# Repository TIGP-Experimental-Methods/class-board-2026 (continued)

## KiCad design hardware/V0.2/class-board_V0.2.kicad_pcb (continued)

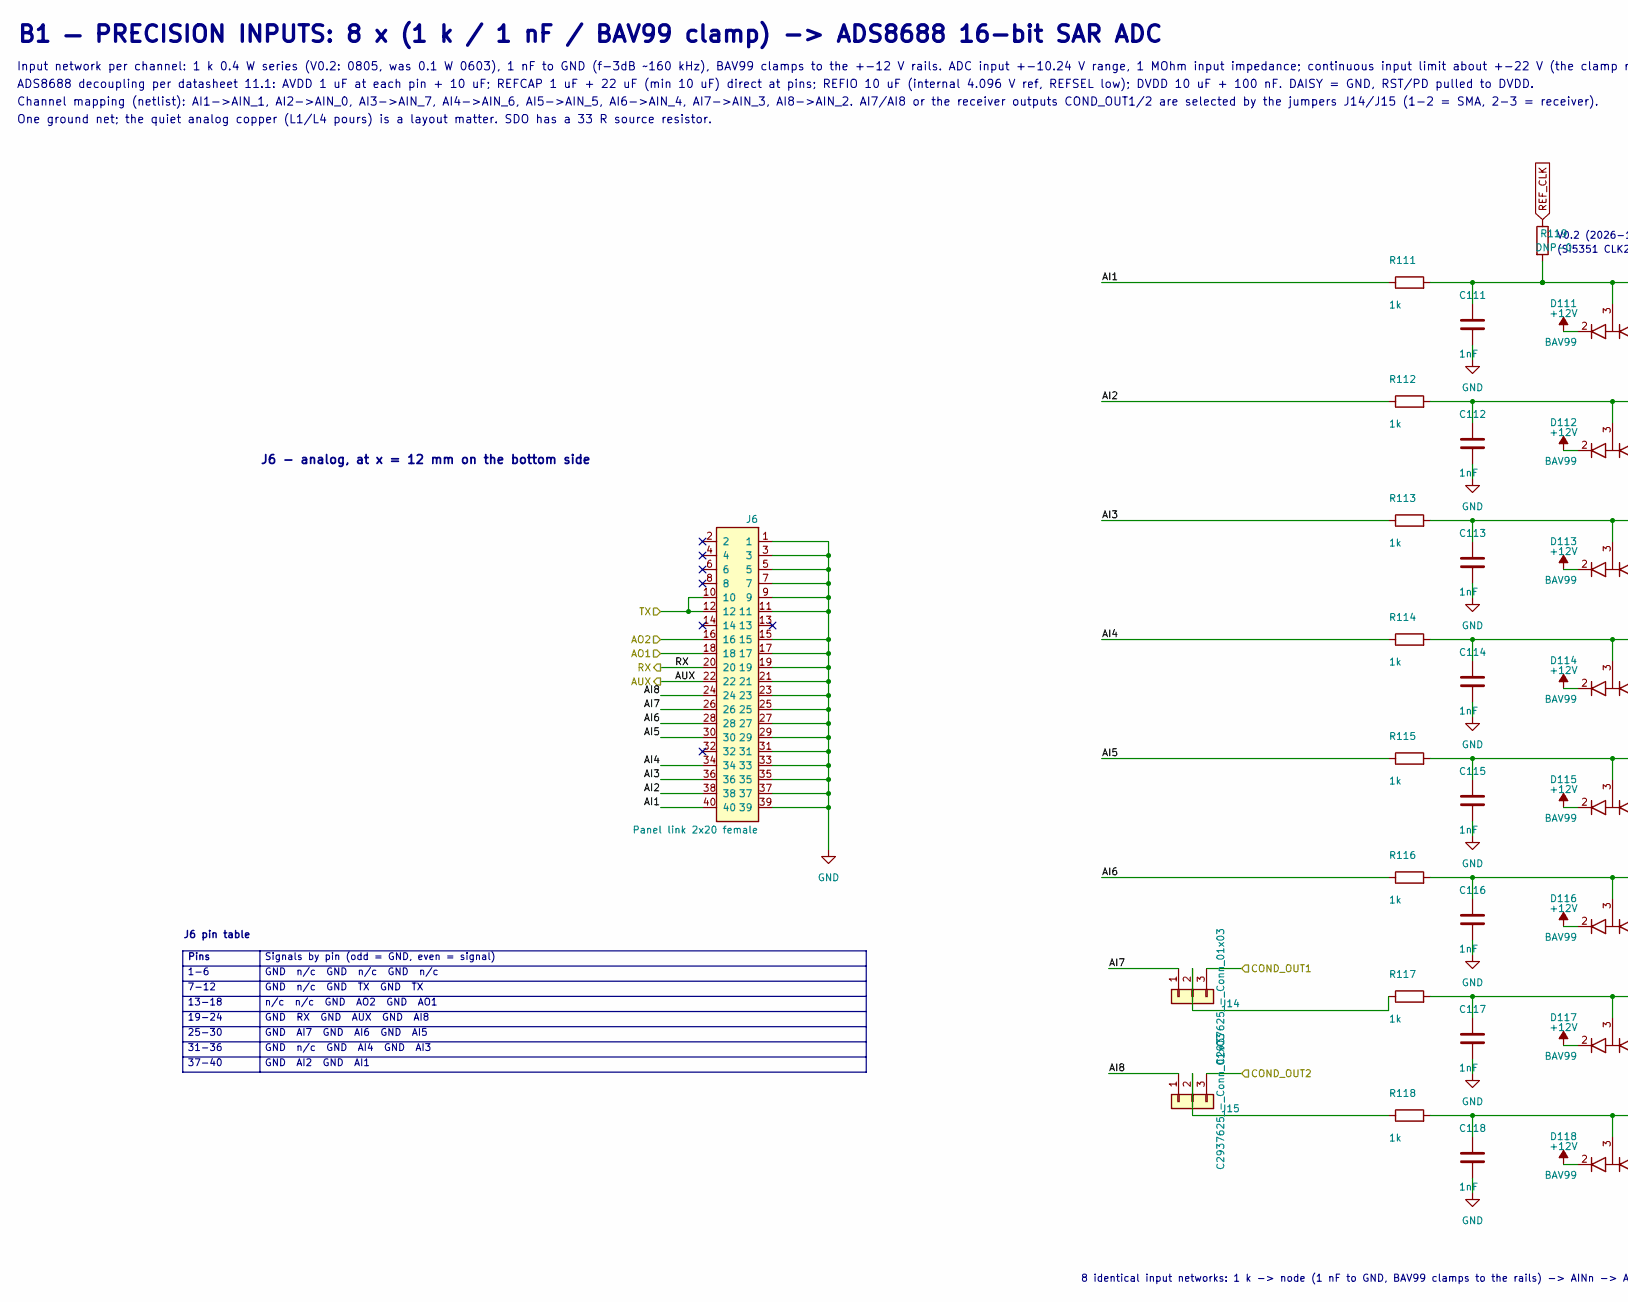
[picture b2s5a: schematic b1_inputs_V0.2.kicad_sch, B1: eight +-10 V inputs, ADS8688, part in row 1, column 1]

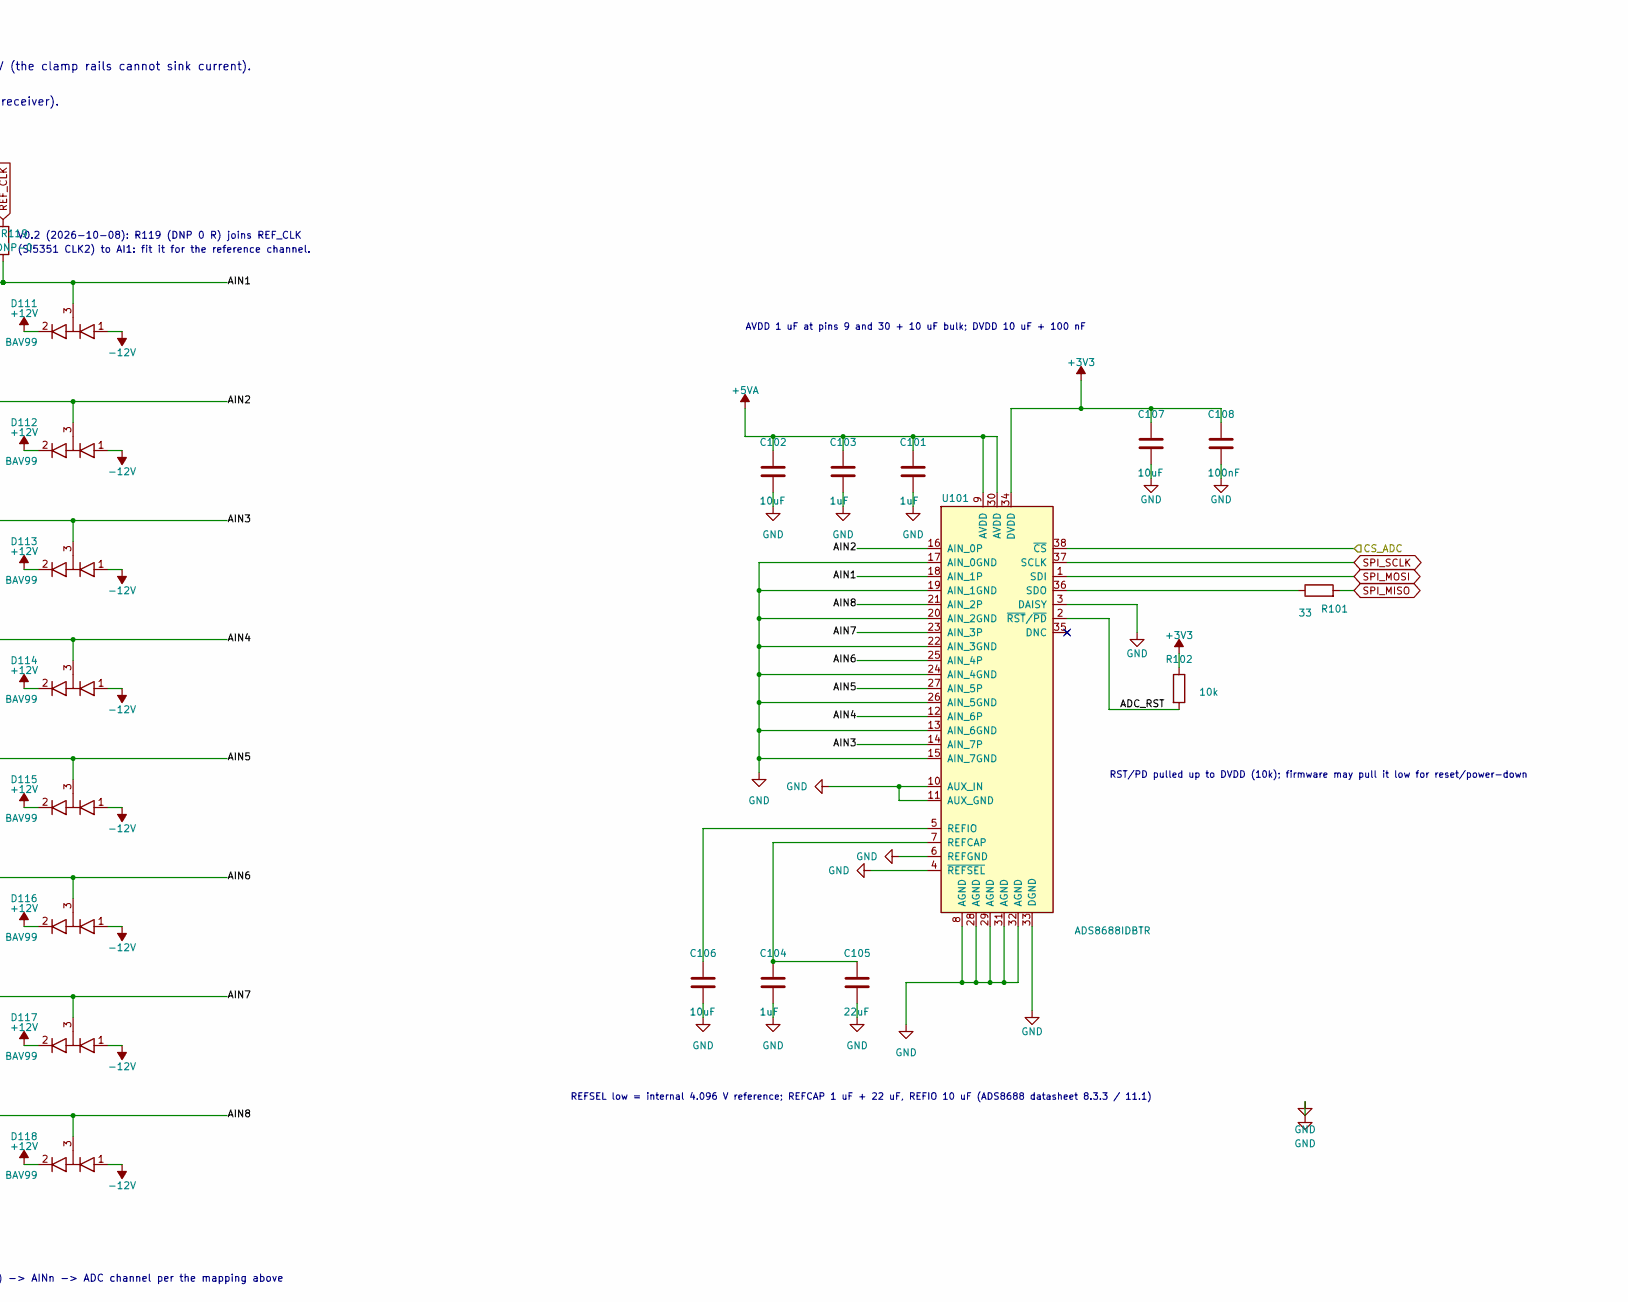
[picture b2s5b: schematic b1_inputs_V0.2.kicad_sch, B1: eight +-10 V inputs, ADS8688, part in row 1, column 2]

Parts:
C101, C103, C104: 1uF; C_0603_1608Metric; MPN CL10A105KB8NNNC; LCSC C15849
C102, C106, C107: 10uF; C_0805_2012Metric; MPN CL21A106KAYNNNE; LCSC C15850
C105: 22uF; C_1206_3216Metric; MPN CL31A226KAHNNNE; LCSC C12891
C108: 100nF; C_0603_1608Metric; MPN CC0603KRX7R9BB104; LCSC C14663
C111, C112, C113, C114, C115, C116, C117, C118: 1nF; C_0603_1608Metric; MPN CL10B102KB8NNNC; LCSC C1588
D111, D112, D113, D114, D115, D116, D117, D118: BAV99; SOT-23-3_L2.9-W1.6-P1.90-LS2.8-BR; MPN BAV99,215; LCSC C2500
J6: Panel link 2x20 female; PinSocket_2x20_P2.54mm_Vertical; MPN 2.54-2*20P (8.5 mm); LCSC C5124634
J14, J15: C2937625_-_Conn_01x03; C2937625-HDR-TH_3P-P2.54-V-M; LCSC C2937625
R101: 33; R_0603_1608Metric; MPN 0603WAF330JT5E; LCSC C23140
R102: 10k; R_0603_1608Metric; MPN 0603WAF1002T5E; LCSC C25804
R111, R112, R113, R114, R115, R116, R117, R118: 1k; R_0805_2012Metric; MPN ESR10EZPF1001; LCSC C510097
R119: DNP-0; R_0603_1608Metric; MPN 0603WAF0000T5E; JLC_CLASS Basic
U101: ADS8688IDBTR; TSSOP-38_L9.7-W4.4-P0.50-LS6.4-BL; MPN ADS8688IDBTR; LCSC C527390

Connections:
+3V3: C107.1, C108.1, R102.1, U101.34 (DVDD); also elsewhere on the board
+5VA: C101.1, C102.1, C103.1, U101.9 (AVDD), U101.30 (AVDD); also elsewhere on the board
/b1_inputs/ADC_RST: R102.2, U101.2 (~RST/~PD)
/b1_inputs/AI1: J6.40, R111.1
/b1_inputs/AI2: J6.38, R112.1
/b1_inputs/AI3: J6.36, R113.1
/b1_inputs/AI4: J6.34, R114.1
/b1_inputs/AI5: J6.30, R115.1
/b1_inputs/AI6: J6.28, R116.1
/b1_inputs/AI7: J6.26, J14.1
/b1_inputs/AI8: J6.24, J15.1
/b1_inputs/AIN1: C111.1, D111.3 (COM), R111.2, R119.2, U101.18 (AIN_1P)
/b1_inputs/AIN2: C112.1, D112.3 (COM), R112.2, U101.16 (AIN_0P)
/b1_inputs/AIN3: C113.1, D113.3 (COM), R113.2, U101.14 (AIN_7P)
/b1_inputs/AIN4: C114.1, D114.3 (COM), R114.2, U101.12 (AIN_6P)
/b1_inputs/AIN5: C115.1, D115.3 (COM), R115.2, U101.27 (AIN_5P)
/b1_inputs/AIN6: C116.1, D116.3 (COM), R116.2, U101.25 (AIN_4P)
/b1_inputs/AIN7: C117.1, D117.3 (COM), R117.2, U101.23 (AIN_3P)
/b1_inputs/AIN8: C118.1, D118.3 (COM), R118.2, U101.21 (AIN_2P)
/b1_inputs/AO1: J6.18; also elsewhere on the board
/b1_inputs/AO2: J6.16; also elsewhere on the board
/b1_inputs/AUX: J6.22; also elsewhere on the board
/b1_inputs/COND_OUT1: J14.3; also elsewhere on the board
/b1_inputs/COND_OUT2: J15.3; also elsewhere on the board
/b1_inputs/CS_ADC: U101.38 (~CS); also elsewhere on the board
/b1_inputs/RX: J6.20; also elsewhere on the board
/b1_inputs/TX: J6.10, J6.12; also elsewhere on the board
GND: C101.2, C102.2, C103.2, C104.2, C105.2, C106.2, C107.2, C108.2, C111.2, C112.2, C113.2, C114.2, C115.2, C116.2, C117.2, C118.2, J6.1, J6.3, J6.5, J6.7, J6.9, J6.11, J6.15, J6.17, J6.19, J6.21, J6.23, J6.25, J6.27, J6.29, J6.31, J6.33, J6.35, J6.37, J6.39, U101.3 (DAISY), U101.4 (~REFSEL), U101.6 (REFGND), U101.8 (AGND), U101.10 (AUX_IN), U101.11 (AUX_GND), U101.13 (AIN_6GND), U101.15 (AIN_7GND), U101.17 (AIN_0GND), U101.19 (AIN_1GND), U101.20 (AIN_2GND), U101.22 (AIN_3GND), U101.24 (AIN_4GND), U101.26 (AIN_5GND), U101.28 (AGND), U101.29 (AGND), U101.31 (AGND), U101.32 (AGND), U101.33 (DGND); also elsewhere on the board
unnamed: J14.2, R117.1
unnamed: J15.2, R118.1
unnamed: C104.1, C105.1, U101.7 (REFCAP)
unnamed: C106.1, U101.5 (REFIO)
unnamed: R101.1, U101.36 (SDO)
REF_CLK: R119.1; also elsewhere on the board
SPI_MISO: R101.2; also elsewhere on the board
SPI_MOSI: U101.1 (SDI); also elsewhere on the board
SPI_SCLK: U101.37 (SCLK); also elsewhere on the board

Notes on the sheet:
Pins
25-30
37-40
7-12
J6 - analog, at x = 12 mm on the bottom side
31-36
ADS8688 decoupling per datasheet 11.1: AVDD 1 uF at each pin + 10 uF; REFCAP 1 uF + 22 uF (min 10 uF) direct at pins; REFIO 10 uF (internal 4.096 V ref, REFSEL low); DVDD 10 uF + 100 nF. DAISY = GND, RST/PD pulled to DVDD.
13-18
1-6
J6 pin table
19-24
AVDD 1 uF at pins 9 and 30 + 10 uF bulk; DVDD 10 uF + 100 nF
B1 — PRECISION INPUTS: 8 x (1 k / 1 nF / BAV99 clamp) -> ADS8688 16-bit SAR ADC
RST/PD pulled up to DVDD (10k); firmware may pull it low for reset/power-down
REFSEL low = internal 4.096 V reference; REFCAP 1 uF + 22 uF, REFIO 10 uF (ADS8688 datasheet 8.3.3 / 11.1)
Signals by pin (odd = GND, even = signal)
GND n/c GND n/c GND n/c
GND n/c GND TX GND TX
n/c n/c GND AO2 GND AO1
GND RX GND AUX GND AI8
GND AI7 GND AI6 GND AI5
GND n/c GND AI4 GND AI3
GND AI2 GND AI1
Input network per channel: 1 k 0.4 W series (V0.2: 0805, was 0.1 W 0603), 1 nF to GND (f-3dB ~160 kHz), BAV99 clamps to the +-12 V rails. ADC input +-10.24 V range, 1 MOhm input impedance; continuous input limit about +-22 V (the clamp rails cannot sink current).
Channel mapping (netlist): AI1->AIN_1, AI2->AIN_0, AI3->AIN_7, AI4->AIN_6, AI5->AIN_5, AI6->AIN_4, AI7->AIN_3, AI8->AIN_2. AI7/AI8 or the receiver outputs COND_OUT1/2 are selected by the jumpers J14/J15 (1-2 = SMA, 2-3 = receiver).
One ground net; the quiet analog copper (L1/L4 pours) is a layout matter. SDO has a 33 R source resistor.
8 identical input networks: 1 k -> node (1 nF to GND, BAV99 clamps to the rails) -> AINn -> ADC channel per the mapping above
V0.2 (2026-10-08): R119 (DNP 0 R) joins REF_CLK
(Si5351 CLK2) to AI1: fit it for the reference channel.

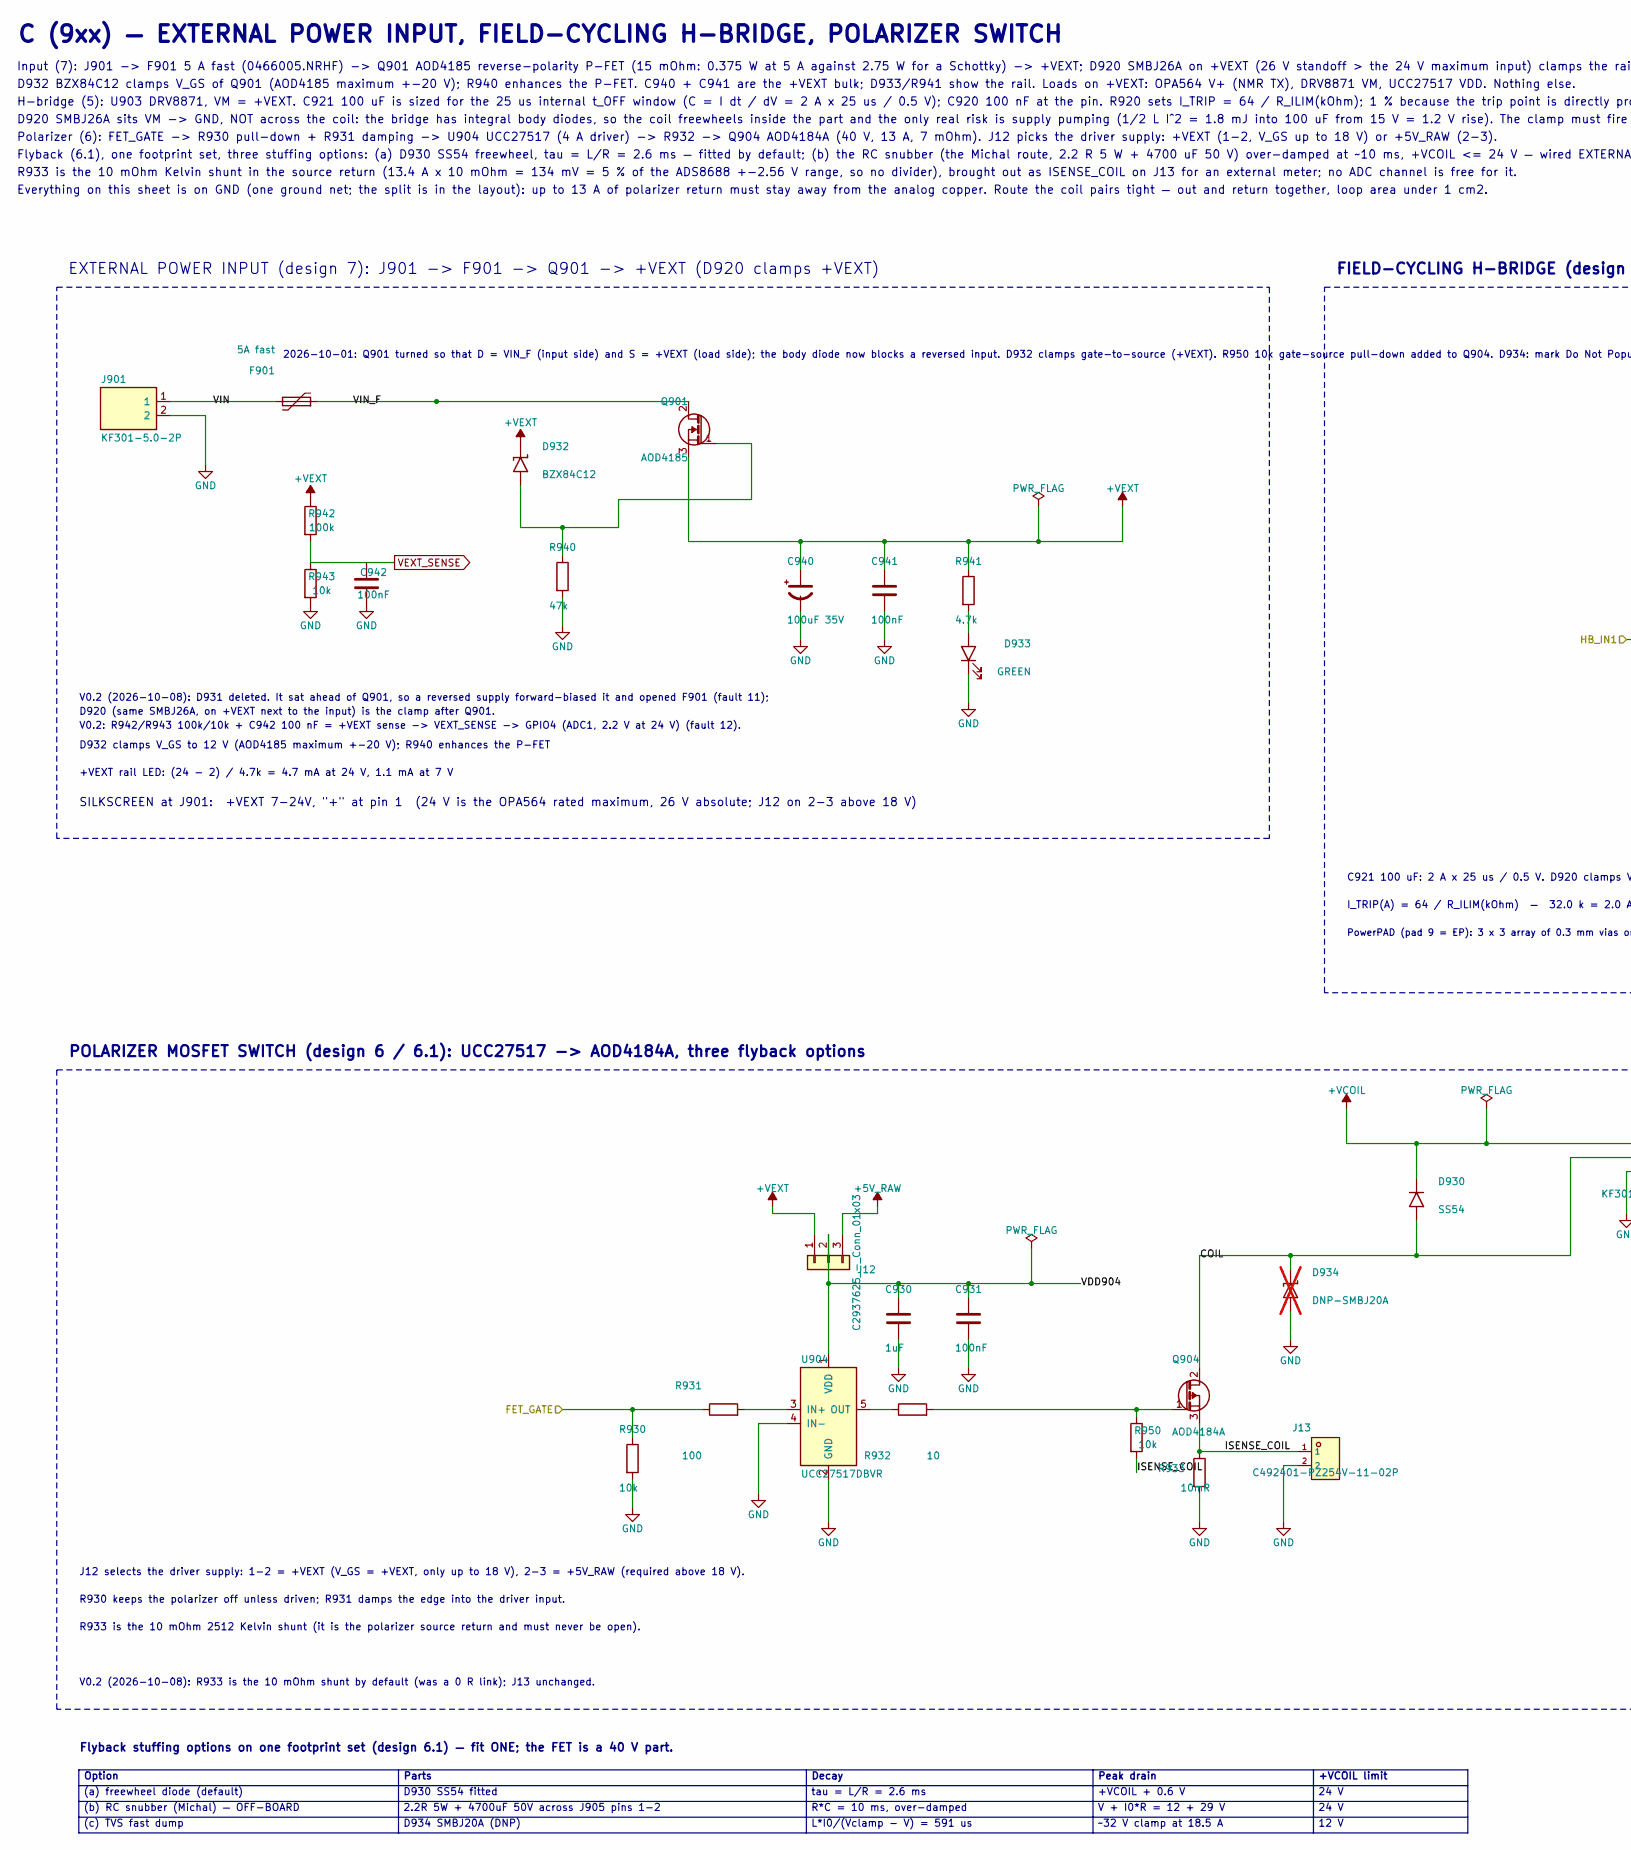
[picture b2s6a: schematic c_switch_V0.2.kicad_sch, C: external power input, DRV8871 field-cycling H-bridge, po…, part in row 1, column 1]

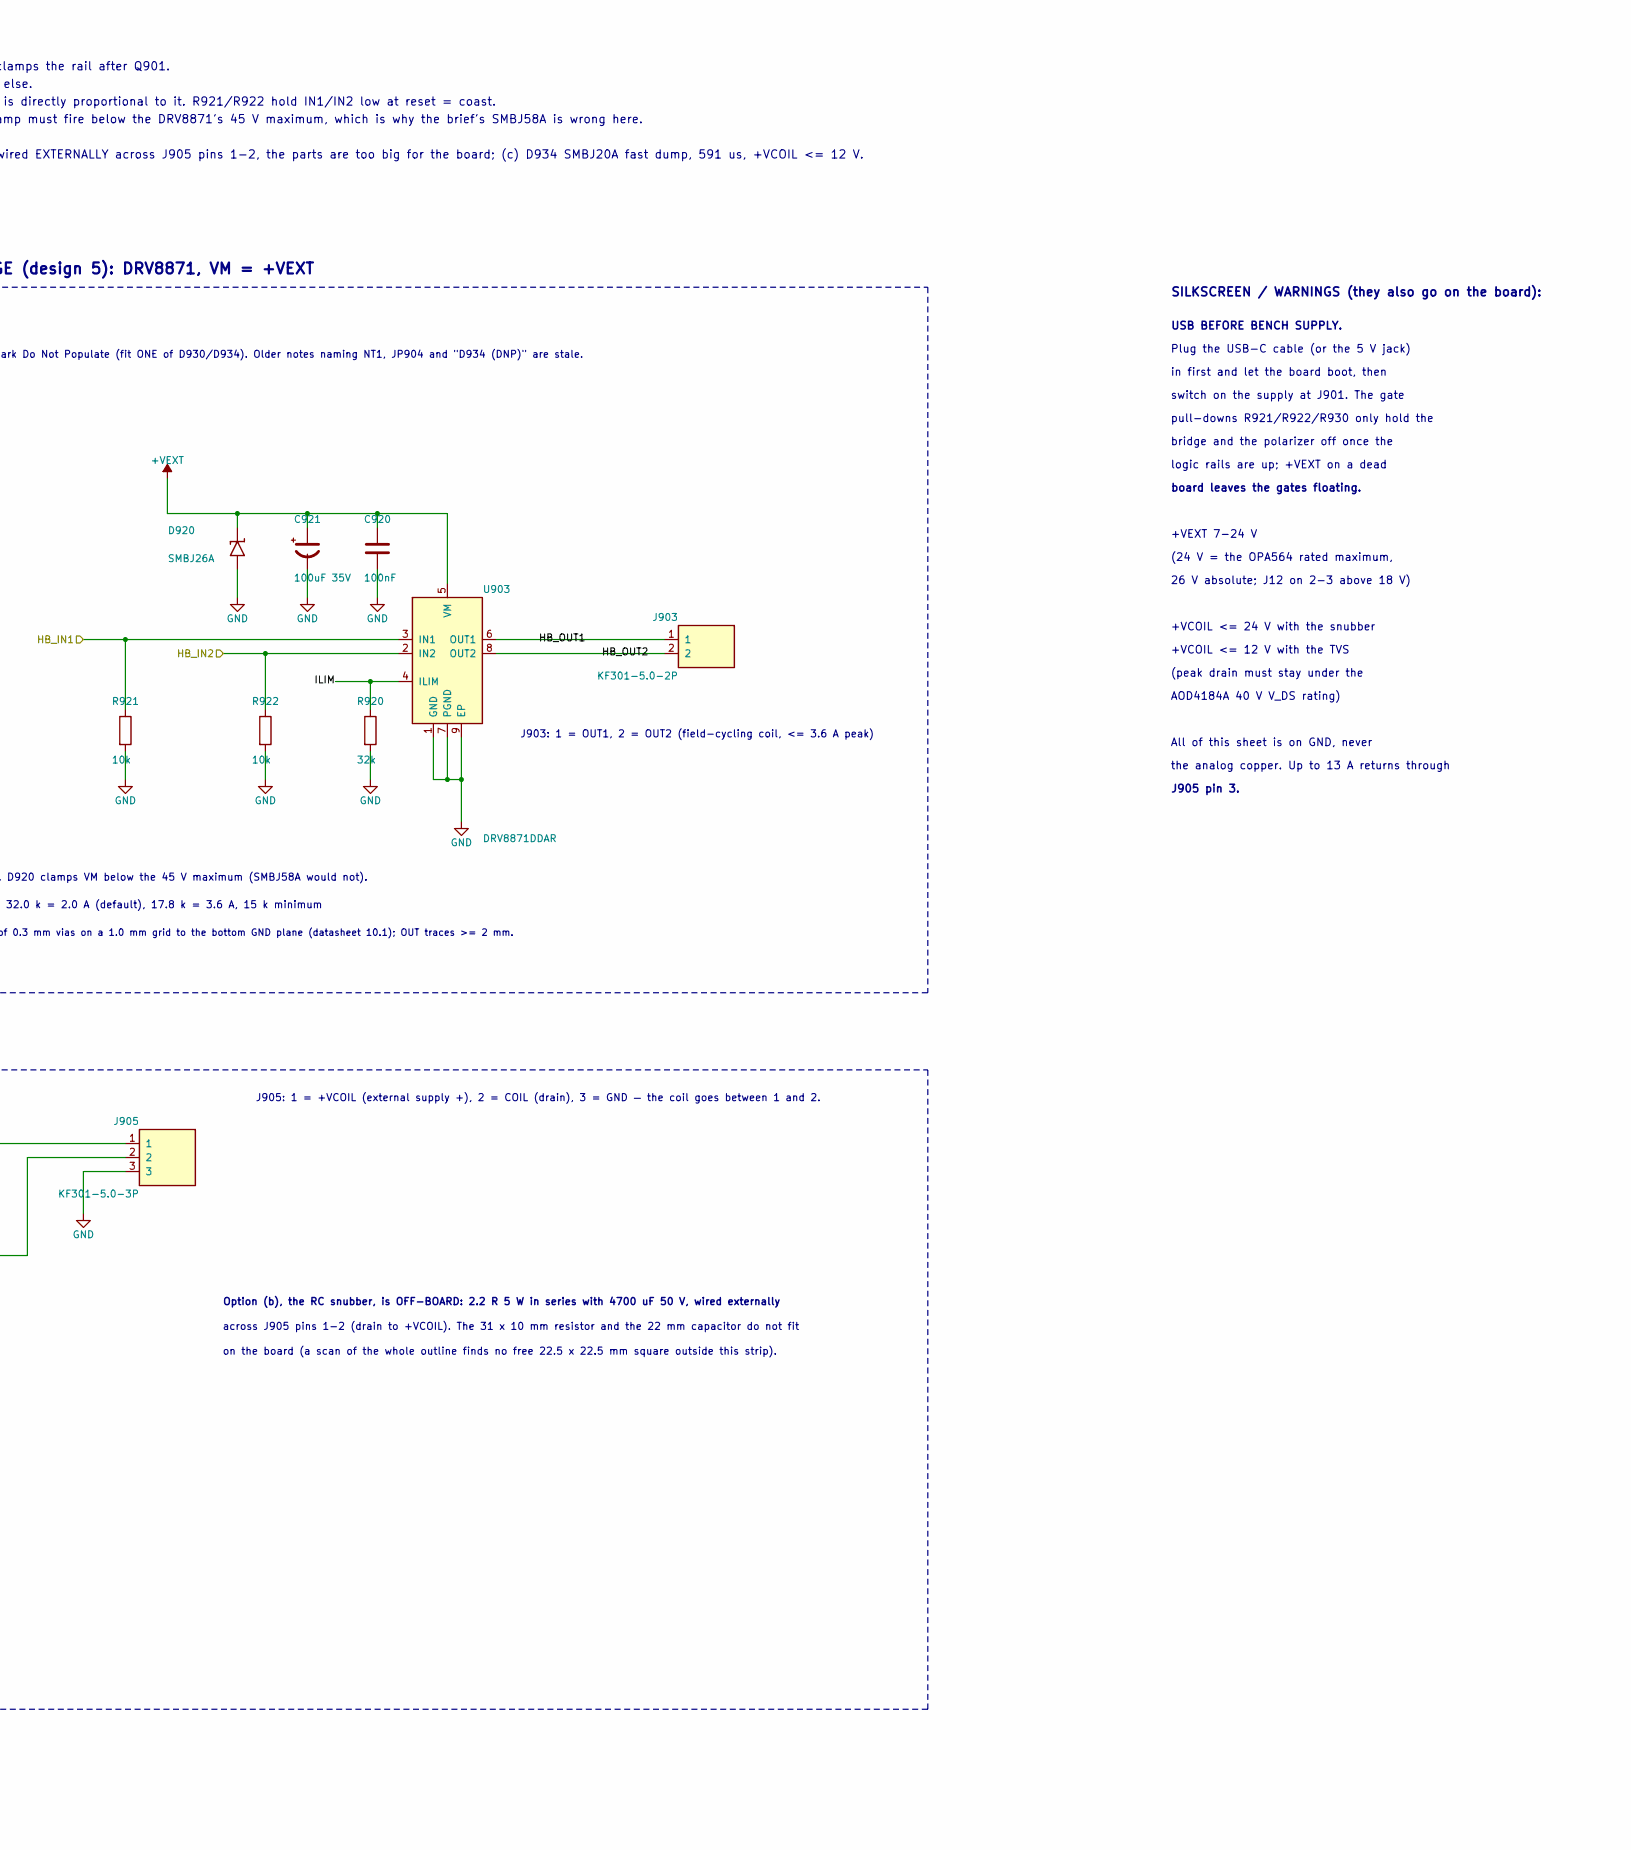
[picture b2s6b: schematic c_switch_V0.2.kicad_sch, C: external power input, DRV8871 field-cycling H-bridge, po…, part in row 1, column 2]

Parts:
C920, C931, C941: 100nF; C_0603_1608Metric; MPN CC0603KRX7R9BB104; LCSC C14663
C921, C940: 100uF 35V; CAP-SMD_BD8.0-L8.3-W8.3-LS9.3-FD; MPN RVT1V101M0810; LCSC C37309
C930: 1uF; C_0603_1608Metric; MPN CL10A105KB8NNNC; LCSC C15849
C942: 100nF; C_0603_1608Metric; MPN CC0603KRX7R9BB104; JLC_CLASS Basic
D920: SMBJ26A; SMB_L4.6-W3.6-LS5.3-RD; MPN SMBJ26A; LCSC C123820
D930: SS54; SMA_L4.4-W2.8-LS5.4-R-RD; MPN SS54; LCSC C22452
D932: BZX84C12; SOT-23-3_L2.9-W1.3-P1.90-LS2.4-BR; MPN BZX84C12; LCSC C112551
D933: GREEN; LED0805-R-RD; MPN KT-0805G; LCSC C2297
D934: DNP-SMBJ20A; SMB_L4.6-W3.6-LS5.3-RD; MPN SMBJ20A; LCSC C294873; not fitted
F901: 5A fast; F1206; MPN 0466005.NRHF; LCSC C57525
J12: C2937625_-_Conn_01x03; C2937625-HDR-TH_3P-P2.54-V-M; LCSC C2937625
J13: C492401-PZ254V-11-02P; C492401-HDR-TH_2P-P2.54-V-M; LCSC C492401
J901, J903: KF301-5.0-2P; CONN-TH_P5.00_KF301-5.0-2P; MPN KF301-5.0-2P; LCSC C474881
J905: KF301-5.0-3P; CONN-TH_3P-P5.00_KF301-5.0-3P; MPN KF301-5.0-3P; LCSC C474882
Q901: AOD4185; TO-252-3_L6.6-W6.1-P4.57-LS9.9-BR-CW; MPN AOD4185; LCSC C400894
Q904: AOD4184A; TO-252-2_L6.6-W6.1-P4.57-LS9.9-TL-CW; MPN AOD4184A; LCSC C99124
R920: 32k; R_0603_1608Metric; MPN RT0603BRD0732KL; LCSC C861325
R921, R922, R930: 10k; R_0603_1608Metric; MPN 0603WAF1002T5E; LCSC C25804
R931: 100; R_0603_1608Metric; MPN 0603WAF1000T5E; LCSC C22775
R932: 10; R_0603_1608Metric; MPN 0603WAF100JT5E; LCSC C22859
R933: 10mR; R_2512_6332Metric; MPN GX2512-2W-10mR-1%; LCSC C500718
R940: 47k; R_0603_1608Metric; MPN 0603WAF4702T5E; LCSC C25819
R941: 4.7k; R_0603_1608Metric; MPN 0603WAF4701T5E; LCSC C23162
R942: 100k; R_0603_1608Metric; MPN 0603WAF1003T5E; JLC_CLASS Basic
R943: 10k; R_0603_1608Metric; MPN 0603WAF1002T5E; JLC_CLASS Basic
R950: 10k; R_0603_1608Metric; LCSC C25804
U903: DRV8871DDAR; SO-8_L4.9-W3.9-P1.27-LS6.0-BL-EP; MPN DRV8871DDAR; LCSC C75864
U904: UCC27517DBVR; SOT-23-5_L3.0-W1.7-P0.95-LS2.8-BR; MPN UCC27517DBVR; LCSC C20623191

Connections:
/base_mcu/FET_GATE: R930.1, R931.1; also elsewhere on the board
/base_mcu/HB_IN1: R921.1, U903.3 (IN1); also elsewhere on the board
/base_mcu/HB_IN2: R922.1, U903.2 (IN2); also elsewhere on the board
/c_switch/COIL: D930.1 (A), D934.1 (K), J905.2, Q904.2 (D)
/c_switch/HB_OUT1: J903.1, U903.6 (OUT1)
/c_switch/HB_OUT2: J903.2, U903.8 (OUT2)
/c_switch/ILIM: R920.1, U903.4 (ILIM)
/c_switch/ISENSE_COIL: J13.1, Q904.3 (S), R933.1, R950.2
/c_switch/VIN: F901.1, J901.1
/c_switch/VIN_F: F901.2, Q901.2 (D)
GND: C920.2, C921.2, C930.2, C931.2, C940.2, C941.2, C942.2, D920.2 (A), D933.2 (A), D934.2 (A), J13.2, J901.2, J905.3, R920.2, R921.2, R922.2, R930.2, R933.2, R940.2, R943.2, U903.1 (GND), U903.7 (PGND), U903.9 (EP), U904.2 (GND), U904.4 (IN-); also elsewhere on the board
unnamed: D932.1 (A), Q901.1 (G), R940.1
unnamed: D933.1 (K), R941.2
unnamed: Q904.1 (G), R932.2, R950.1
unnamed: R931.2, U904.3 (IN+)
unnamed: R932.1, U904.5 (OUT)
VEXT_SENSE: C942.1, R942.2, R943.1; also elsewhere on the board

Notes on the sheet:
Option (b), the RC snubber, is OFF-BOARD: 2.2 R 5 W in series with 4700 uF 50 V, wired externally
V + I0*R = 12 + 29 V
+VCOIL limit
AOD4184A 40 V V_DS rating)
L*I0/(Vclamp - V) = 591 us
FIELD-CYCLING H-BRIDGE (design 5): DRV8871, VM = +VEXT
tau = L/R = 2.6 ms
USB BEFORE BENCH SUPPLY.
R930 keeps the polarizer off unless driven; R931 damps the edge into the driver input.
D934 SMBJ20A (DNP)
D932 clamps V_GS to 12 V (AOD4185 maximum +-20 V); R940 enhances the P-FET
Flyback (6.1), one footprint set, three stuffing options: (a) D930 SS54 freewheel, tau = L/R = 2.6 ms — fitted by default; (b) the RC snubber (the Michal route, 2.2 R 5 W + 4700 uF 50 V) over-damped at ~10 ms, +VCOIL <= 24 V — wired EXTERNALLY across J905 pins 1-2, the parts are too big for the boa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
D930 SS54 fitted
2026-10-01: Q901 turned so that D = VIN_F (input side) and S = +VEXT (load side); the body diode now blocks a reversed input. D932 clamps gate-to-source (+VEXT). R950 10k gate-source pull-down added to Q904. D934: mark Do Not Populate (fit ONE of D930/D934). Older notes naming NT1, JP904 and "D934 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
12 V
logic rails are up; +VEXT on a dead
2.2R 5W + 4700uF 50V across J905 pins 1-2
24 V
C921 100 uF: 2 A x 25 us / 0.5 V. D920 clamps VM below the 45 V maximum (SMBJ58A would not).
(c) TVS fast dump
(a) freewheel diode (default)
switch on the supply at J901. The gate
bridge and the polarizer off once the
+VCOIL <= 12 V with the TVS
Parts
across J905 pins 1-2 (drain to +VCOIL). The 31 x 10 mm resistor and the 22 mm capacitor do not fit
Peak drain
+VEXT rail LED: (24 - 2) / 4.7k = 4.7 mA at 24 V, 1.1 mA at 7 V
D920 SMBJ26A sits VM -> GND, NOT across the coil: the bridge has integral body diodes, so the coil freewheels inside the part and the only real risk is supply pumping (1/2 L I^2 = 1.8 mJ into 100 uF from 15 V = 1.2 V rise). The clamp must fire below the DRV8871's 45 V maximum, which is why the brie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
Decay
I_TRIP(A) = 64 / R_ILIM(kOhm) — 32.0 k = 2.0 A (default), 17.8 k = 3.6 A, 15 k minimum
Flyback stuffing options on one footprint set (design 6.1) — fit ONE; the FET is a 40 V part.
Plug the USB-C cable (or the 5 V jack)
Option
in first and let the board boot, then
POLARIZER MOSFET SWITCH (design 6 / 6.1): UCC27517 -> AOD4184A, three flyback options
All of this sheet is on GND, never
on the board (a scan of the whole outline finds no free 22.5 x 22.5 mm square outside this strip).
H-bridge (5): U903 DRV8871, VM = +VEXT. C921 100 uF is sized for the 25 us internal t_OFF window (C = I dt / dV = 2 A x 25 us / 0.5 V); C920 100 nF at the pin. R920 sets I_TRIP = 64 / R_ILIM(kOhm); 1 % because the trip point is directly proportional to it. R921/R922 hold IN1/IN2 low at reset = coas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
board leaves the gates floating.

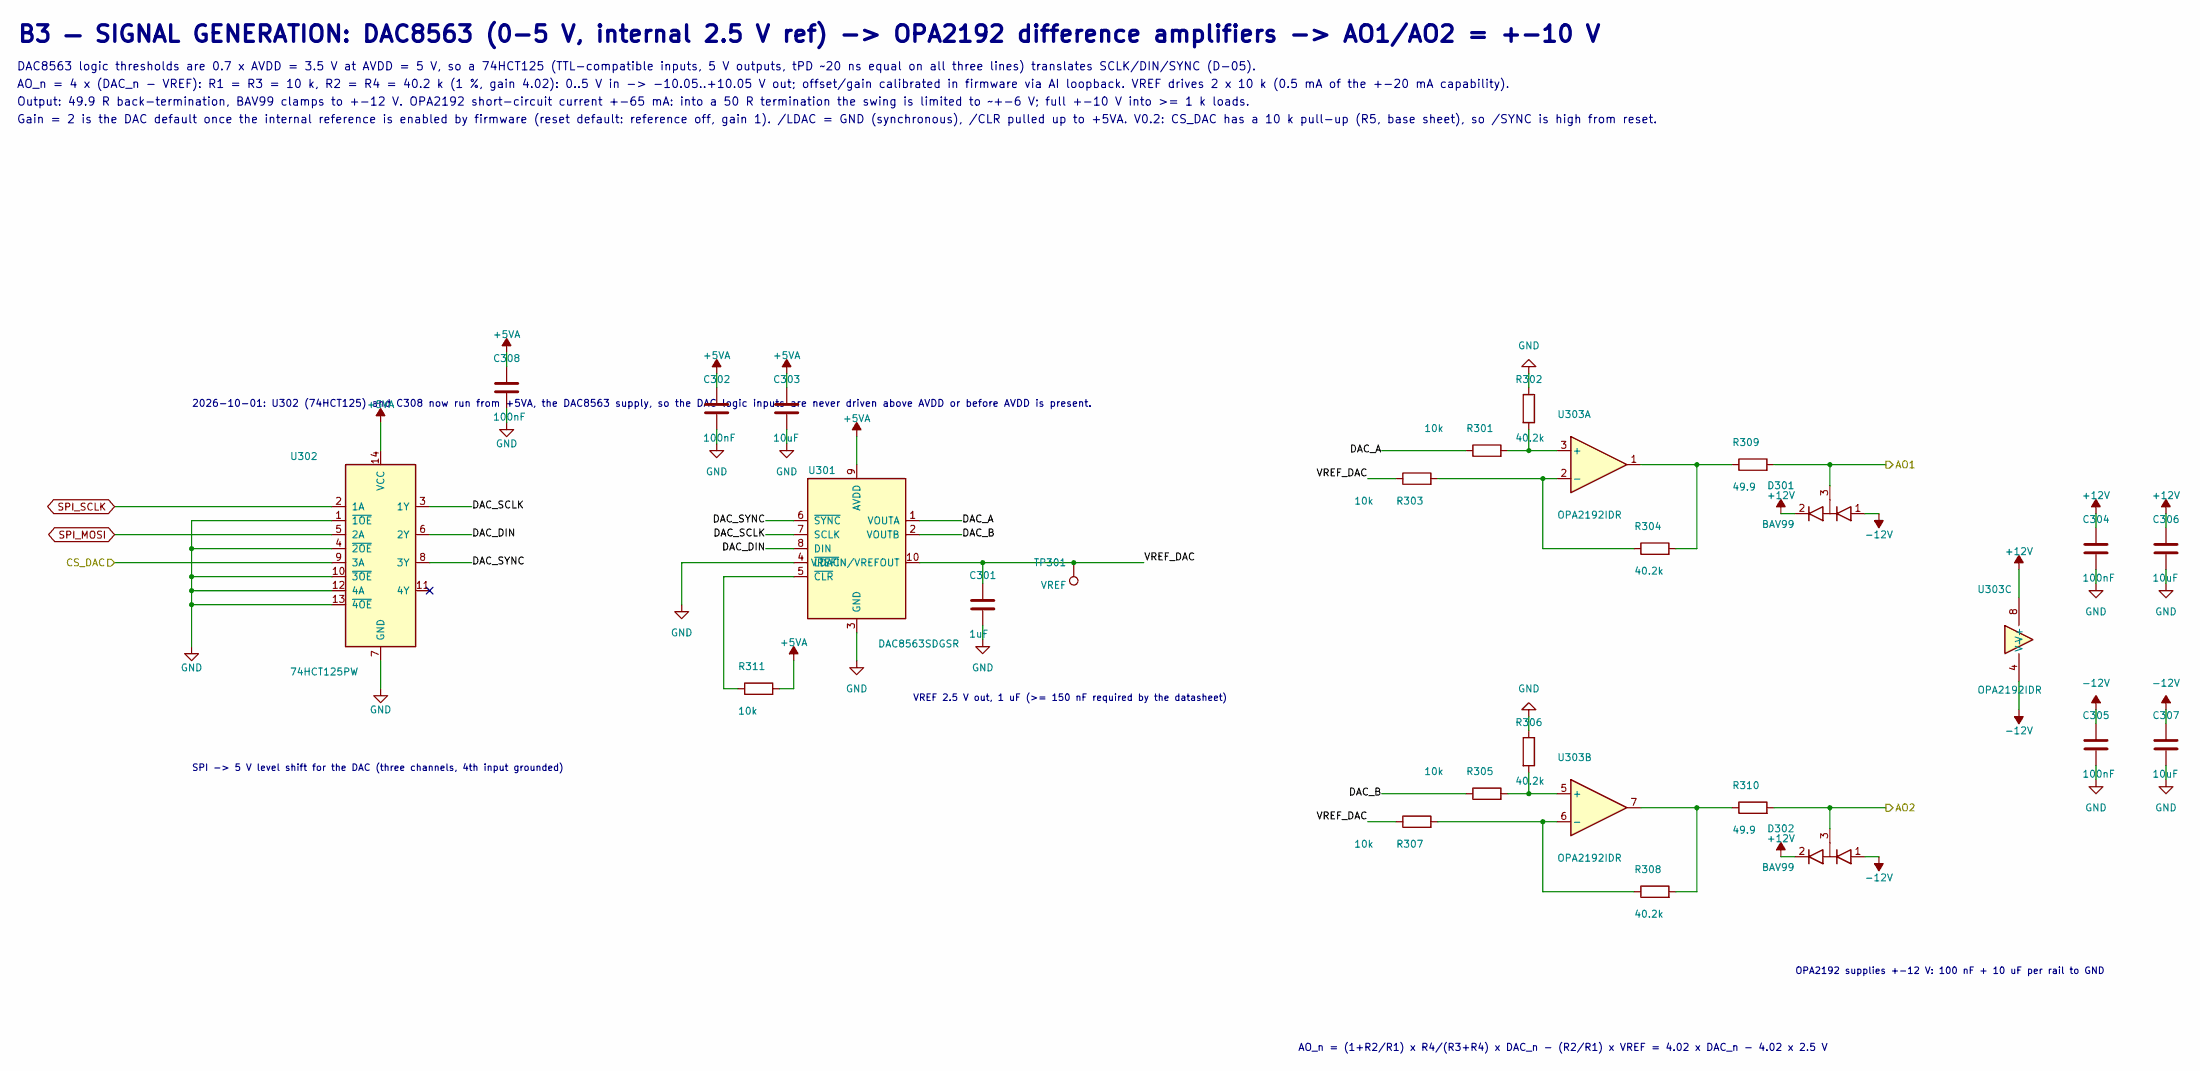
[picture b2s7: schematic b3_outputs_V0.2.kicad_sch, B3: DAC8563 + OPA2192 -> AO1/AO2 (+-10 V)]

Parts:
C301: 1uF; C_0603_1608Metric; MPN CL10A105KB8NNNC; LCSC C15849
C302, C304, C305, C308: 100nF; C_0603_1608Metric; MPN CC0603KRX7R9BB104; LCSC C14663
C303, C306, C307: 10uF; C_0805_2012Metric; MPN CL21A106KAYNNNE; LCSC C15850
D301, D302: BAV99; SOT-23-3_L2.9-W1.6-P1.90-LS2.8-BR; MPN BAV99,215; LCSC C2500
R301, R303, R305, R307, R311: 10k; R_0603_1608Metric; MPN 0603WAF1002T5E; LCSC C25804
R302, R304, R306, R308: 40.2k; R_0603_1608Metric; MPN 0603WAF4022T5E; LCSC C12447
R309, R310: 49.9; R_0603_1608Metric; MPN 0603WAF499JT5E; LCSC C23185
TP301: VREF; TestPoint_Pad_D1.5mm
U301: DAC8563SDGSR; VSSOP-10_L3.0-W3.0-P0.50-LS4.9-BL; MPN DAC8563SDGSR; LCSC C1554729
U302: 74HCT125PW; TSSOP-14_L5.0-W4.4-P0.65-LS6.4-BL; MPN 74HCT125PW,118; LCSC C131316
U303: OPA2192IDR; SOIC-8_L4.9-W3.9-P1.27-LS6.0-BL; MPN OPA2192IDR; LCSC C110074

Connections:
+5VA: C302.1, C303.1, C308.1, R311.2, U301.9 (AVDD), U302.14 (VCC); also elsewhere on the board
/b1_inputs/AO1: D301.3 (COM), R309.2; also elsewhere on the board
/b1_inputs/AO2: D302.3 (COM), R310.2; also elsewhere on the board
/b3_outputs/CS_DAC: U302.9 (3A); also elsewhere on the board
/b3_outputs/DAC_A: R301.1, U301.1 (VOUTA)
/b3_outputs/DAC_B: R305.1, U301.2 (VOUTB)
/b3_outputs/DAC_DIN: U301.8 (DIN), U302.6 (2Y)
/b3_outputs/DAC_SCLK: U301.7 (SCLK), U302.3 (1Y)
/b3_outputs/DAC_SYNC: U301.6 (~SYNC), U302.8 (3Y)
/b3_outputs/VREF_DAC: C301.1, R303.1, R307.1, TP301.1 (1_1), U301.10 (VREFIN/VREFOUT)
GND: C301.2, C302.2, C303.2, C304.2, C305.2, C306.2, C307.2, C308.2, R302.1, R306.1, U301.3 (GND), U301.4 (~LDAC), U302.1 (~1OE), U302.4 (~2OE), U302.7 (GND), U302.10 (~3OE), U302.12 (4A), U302.13 (~4OE); also elsewhere on the board
unnamed: R304.2, R309.1, U303.1
unnamed: R308.2, R310.1, U303.7
unnamed: R311.1, U301.5 (~CLR)
unnamed: R301.2, R302.2, U303.3 (+)
unnamed: R303.2, R304.1, U303.2 (-)
unnamed: R305.2, R306.2, U303.5 (+)
unnamed: R307.2, R308.1, U303.6 (-)
SPI_MOSI: U302.5 (2A); also elsewhere on the board
SPI_SCLK: U302.2 (1A); also elsewhere on the board

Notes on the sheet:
B3 — SIGNAL GENERATION: DAC8563 (0-5 V, internal 2.5 V ref) -> OPA2192 difference amplifiers -> AO1/AO2 = +-10 V
AO_n = 4 x (DAC_n - VREF): R1 = R3 = 10 k, R2 = R4 = 40.2 k (1 %, gain 4.02): 0..5 V in -> -10.05..+10.05 V out; offset/gain calibrated in firmware via AI loopback. VREF drives 2 x 10 k (0.5 mA of the +-20 mA capability).
Output: 49.9 R back-termination, BAV99 clamps to +-12 V. OPA2192 short-circuit current +-65 mA: into a 50 R termination the swing is limited to ~+-6 V; full +-10 V into >= 1 k loads.
VREF 2.5 V out, 1 uF (>= 150 nF required by the datasheet)
2026-10-01: U302 (74HCT125) and C308 now run from +5VA, the DAC8563 supply, so the DAC logic inputs are never driven above AVDD or before AVDD is present.
DAC8563 logic thresholds are 0.7 x AVDD = 3.5 V at AVDD = 5 V, so a 74HCT125 (TTL-compatible inputs, 5 V outputs, tPD ~20 ns equal on all three lines) translates SCLK/DIN/SYNC (D-05).
SPI -> 5 V level shift for the DAC (three channels, 4th input grounded)
AO_n = (1+R2/R1) x R4/(R3+R4) x DAC_n - (R2/R1) x VREF = 4.02 x DAC_n - 4.02 x 2.5 V
OPA2192 supplies +-12 V: 100 nF + 10 uF per rail to GND
Gain = 2 is the DAC default once the internal reference is enabled by firmware (reset default: reference off, gain 1). /LDAC = GND (synchronous), /CLR pulled up to +5VA. V0.2: CS_DAC has a 10 k pull-up (R5, base sheet), so /SYNC is high from reset.
